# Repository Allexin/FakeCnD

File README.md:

# FakeCnD
Cashboxes and Dispensers emulators on arduino

This is simple project for cash terminals developers.  
Simple change settings of emulator in config.h, and upload sketch to yours arduino.  
Connect arduino to PC and start testing.  
  
Available emulators:  
Puloon LCDM 2000  
Generic ccnet bill validator  
GEneric cctalk bill validator

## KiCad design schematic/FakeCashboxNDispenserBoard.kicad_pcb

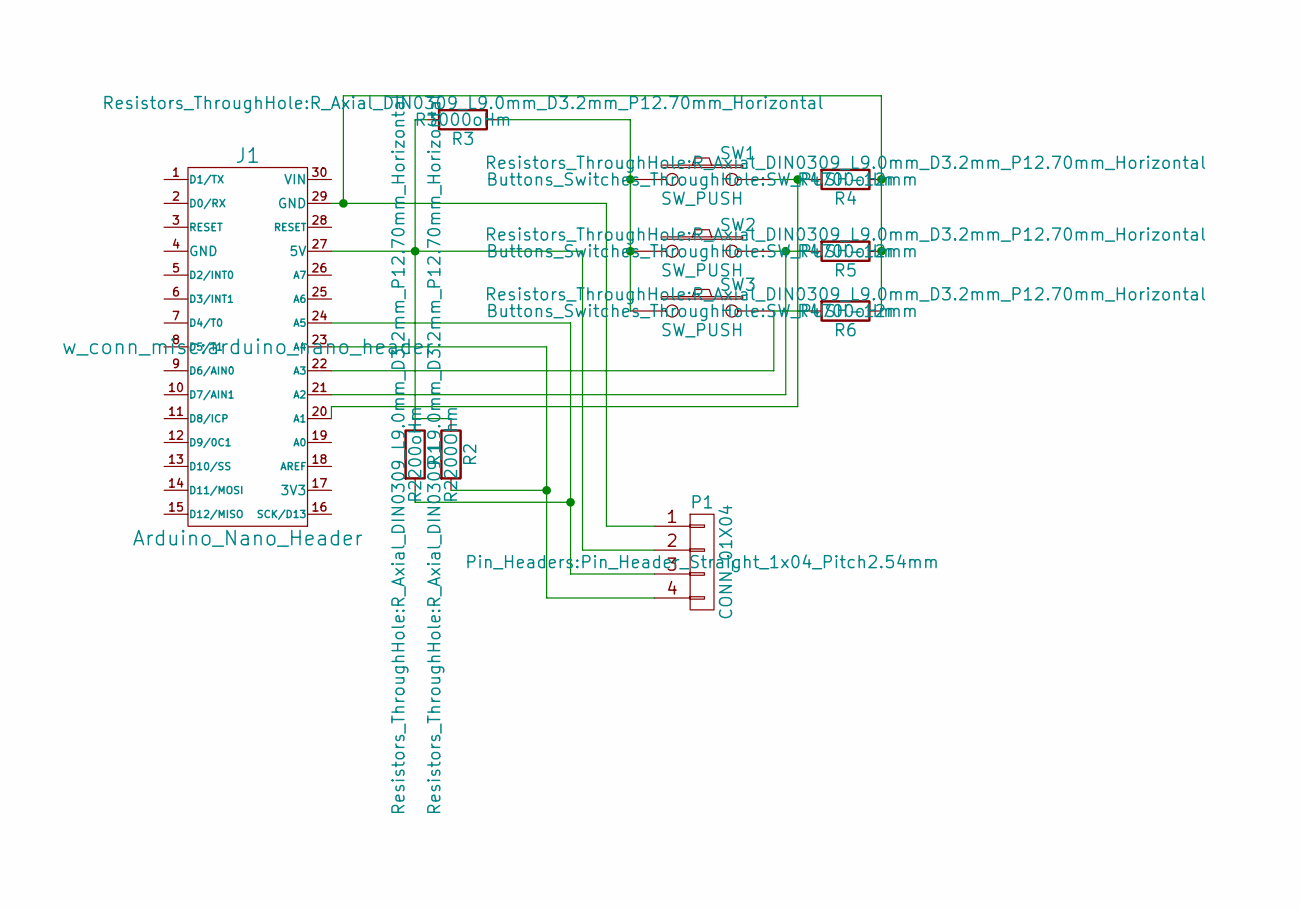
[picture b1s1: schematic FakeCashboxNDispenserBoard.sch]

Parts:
J1: Arduino_Nano_Header; arduino_nano_header
P1: CONN_01X04; Pin_Header_Straight_1x04_Pitch2.54mm
R1: R2200oHm; R_Axial_DIN0309_L9.0mm_D3.2mm_P12.70mm_Horizontal
R2: R2200Ohm; R_Axial_DIN0309_L9.0mm_D3.2mm_P12.70mm_Horizontal
R3: R3000oHm; R_Axial_DIN0309_L9.0mm_D3.2mm_P12.70mm_Horizontal
R4, R5, R6: R4700oHm; R_Axial_DIN0309_L9.0mm_D3.2mm_P12.70mm_Horizontal
SW1, SW2, SW3: SW_PUSH; SW_PUSH-12mm

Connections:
unnamed: J1.20 (A1), R4.2, SW1.2
unnamed: J1.21 (A2), R5.2, SW2.2
unnamed: J1.22 (A3), R6.2, SW3.2
unnamed: J1.23 (A4), P1.4, R2.2
unnamed: J1.24 (A5), P1.3, R1.2
unnamed: J1.27 (5V), P1.2, R1.1, R2.1, R3.2
unnamed: J1.29 (GND), P1.1, R4.1, R5.1, R6.1
unnamed: R3.1, SW1.1, SW2.1, SW3.1

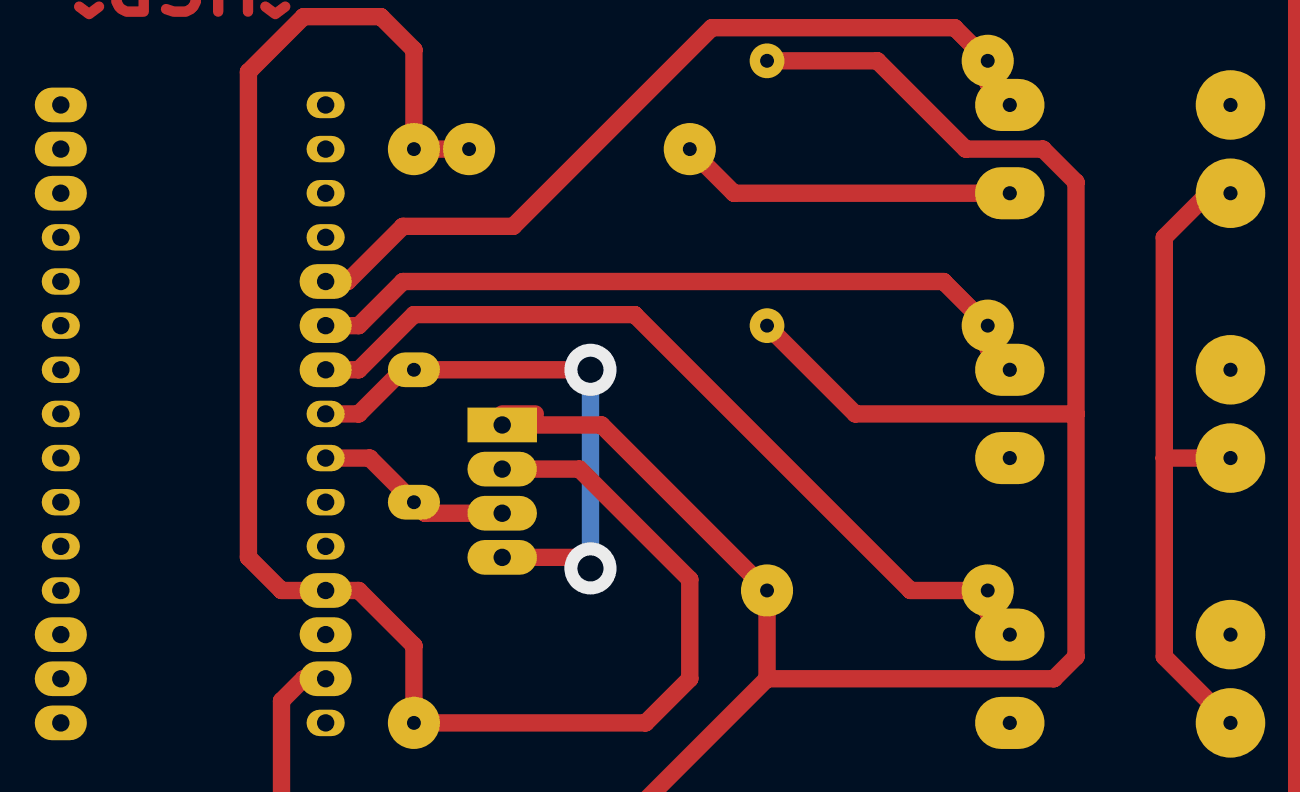
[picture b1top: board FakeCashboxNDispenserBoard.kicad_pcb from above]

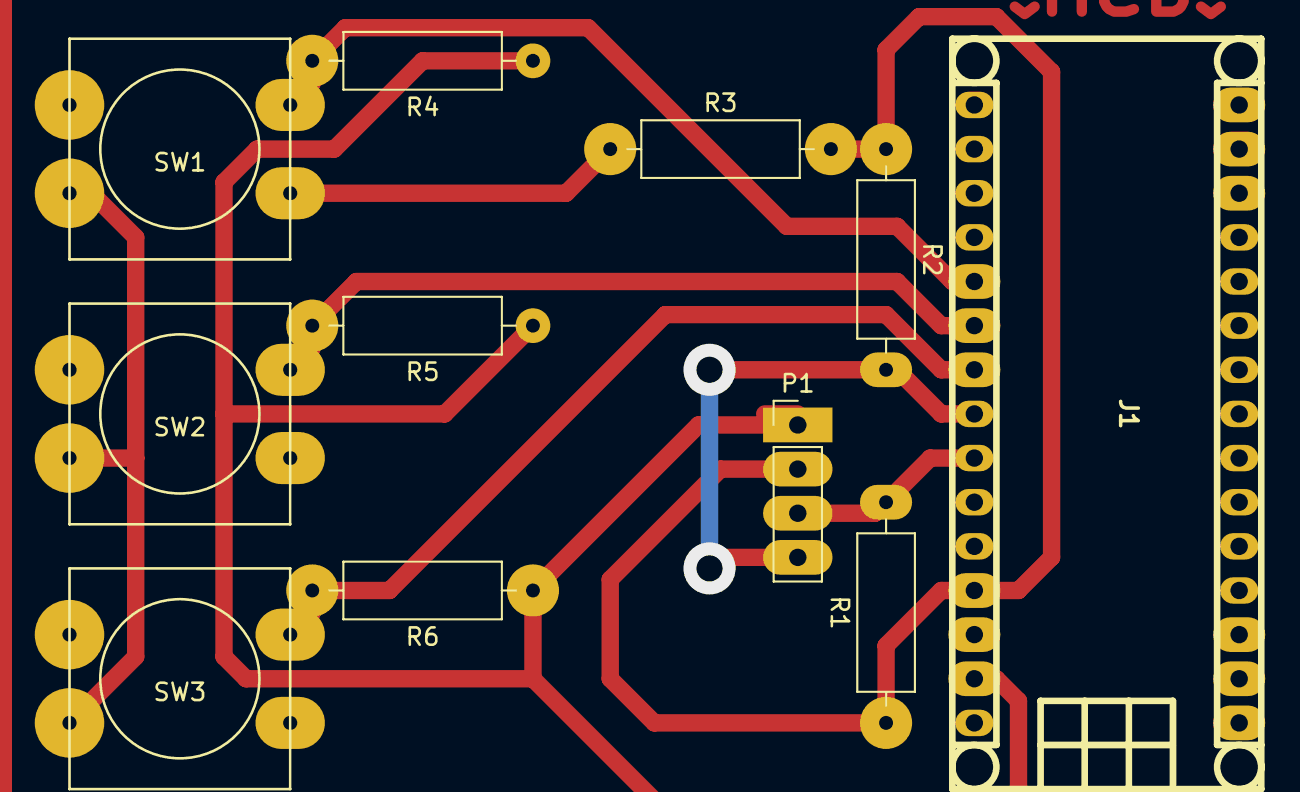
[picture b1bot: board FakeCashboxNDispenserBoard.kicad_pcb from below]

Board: 2 copper layers, 11 parts (11 on the bottom side), 8 nets.

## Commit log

2017-03-21 Add info about ccTalk
